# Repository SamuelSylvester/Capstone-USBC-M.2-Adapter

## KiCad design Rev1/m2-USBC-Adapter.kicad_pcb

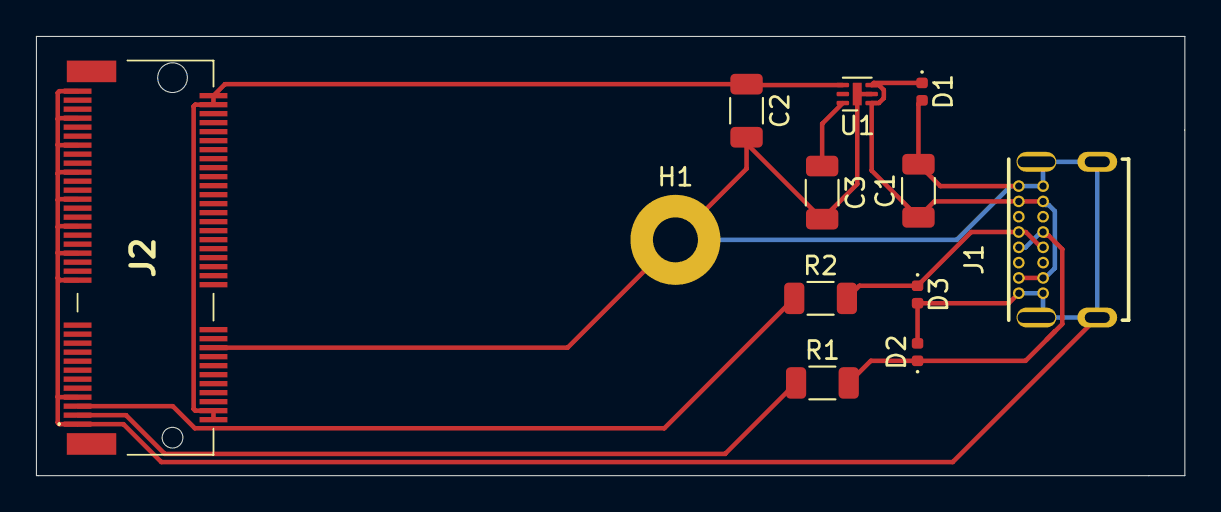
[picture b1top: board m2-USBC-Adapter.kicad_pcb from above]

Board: 2 copper layers, 63.8 x 24.4 mm, 12 parts (0 on the bottom side), 8 nets.

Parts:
C1, C2: 1 u; C_1206_3216Metric
C3: .01 u; C_1206_3216Metric
D1, D2, D3: D_TVS; D_0402_1005Metric
H1: MountingHole_Pad; MountingHole_2.5mm_Pad
J1: USB4085-GF-A_REVA4; GCT_USB4085-GF-A_REVA4
J2: 2199230-4; m2-21992304
R1, R2: 30; R_1206_3216Metric
U1: MIC5353-3.3YMT; MLF-6-1EP_1.6x1.6mm_P0.5mm_EP0.5x1.26mm

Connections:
/3V3: C2.1, J2.2, J2.4, J2.72, J2.74, U1.4
/5V: C1.1, D1.1, J1.A4, J1.A9, J1.B4, J1.B9, U1.1, U1.3
/D_minus_M2: J2.3, R1.1
/D_minus_USB: D2.1, J1.A6, J1.B6, R1.2
/D_plus_M2: J2.5, R2.1
/D_plus_USB: D3.1, J1.A7, J1.B7, R2.2
GND: C1.2, C2.2, C3.2, D1.2, D2.2, D3.2, H1.1, J1.A1, J1.A12, J1.B1, J1.B12, J1.P1, J1.P2, J1.P3, J1.P4, J2.1, J2.7, J2.18, J2.33, J2.39, J2.45, J2.51, J2.57, J2.63, J2.69, J2.75, U1.2, U1.7
unnamed: C3.1, U1.6

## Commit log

2024-01-12 final commit
    The two board versions greated as a USB-C to M.2 adapter for my Senior Capstone Engineering Project
